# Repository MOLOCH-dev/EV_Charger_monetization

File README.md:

# EV_Charger_monetization
Internship under Magnes Motors

# TABLE OF CONTENTS
- [HTTP Webserver on Arduino IDE](#http-webserver-on-arduino-ide)
- [Schematics]
    - [Power Management IC with ESP32](#IC-ESP32)
    - [Current and Voltage Sensor with ESP32](#current-and-voltage-sensor-with-ESP32)

# HTTP Webserver on Arduino IDE

## 1. Flash Code to ESP32

## 2. Connect to WiFi AP "Magnes" using an Android Device

## 3. Go to "http://192.168.4.1" in browser through Android

## 4. Input Watthours and press 'Submit'

## 5. Charge is displayed on the webpage

## 6. Press Back

# IC ESP32

# Current and Voltage Sensor with ESP32

# Flutter App Development

Installation instructions

For Ubuntu 20.04 :
```
    sudo apt purge openjdk-11-jre -y
    sudo apt autoremove
    java -v
    sudo apt update
    sudo apt install openjdk-8-jre
```

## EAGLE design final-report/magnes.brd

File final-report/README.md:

# Final Report

## Instructions:

1. you need to add following zip libraries in arduino library:
	- [ESPAsyncWebServer-master.zip](ESPAsyncWebServer-master.zip)
	- [AsyncTCP-master.zip](AsyncTCP-master.zip)

2. Change ssid and password according to your wifi in the code and then upload the code to esp32.

3. Now open the serial monitor in arduino IDE, copy the ip address given there and paste it in google chrome tab.<br>
Enter your name, required ON time in minutes and current value the power outlet will have started working in arduino serial monitor, you will get the amount to be paid.<br>
**NOTE:** if you by mistakely entered a greater value in minutes, in pcb board, press the switch to restard esp, in design board, power off the adapter and on it again to restart esp. you dont need to flash the code again.

***Precautions:*** Don't touch the pcb board when live ac current is connected to the relay of the board.

## Circuit Diagrams

**If having any doubts in circuit design
Contact Akshat Bhanushali
8080252000**

**Demo videos can be found [here](https://drive.google.com/drive/folders/1dX3jx_bcWb19_J7uATpOkhGvCnvLUn2F)**

## improvement areas

1. current sensor needs be included
2. esp wifi module needs to be used instead of whole esp dev kit
3. remove 7A relay and include 16A omron relay in pcb design
4. include smps so that another socket is not required for adapter
5. try restarting the esp by giving commands over wifi.

## Members:
1. Akshat B.
2. Dhruva G.
3. Anushree S.

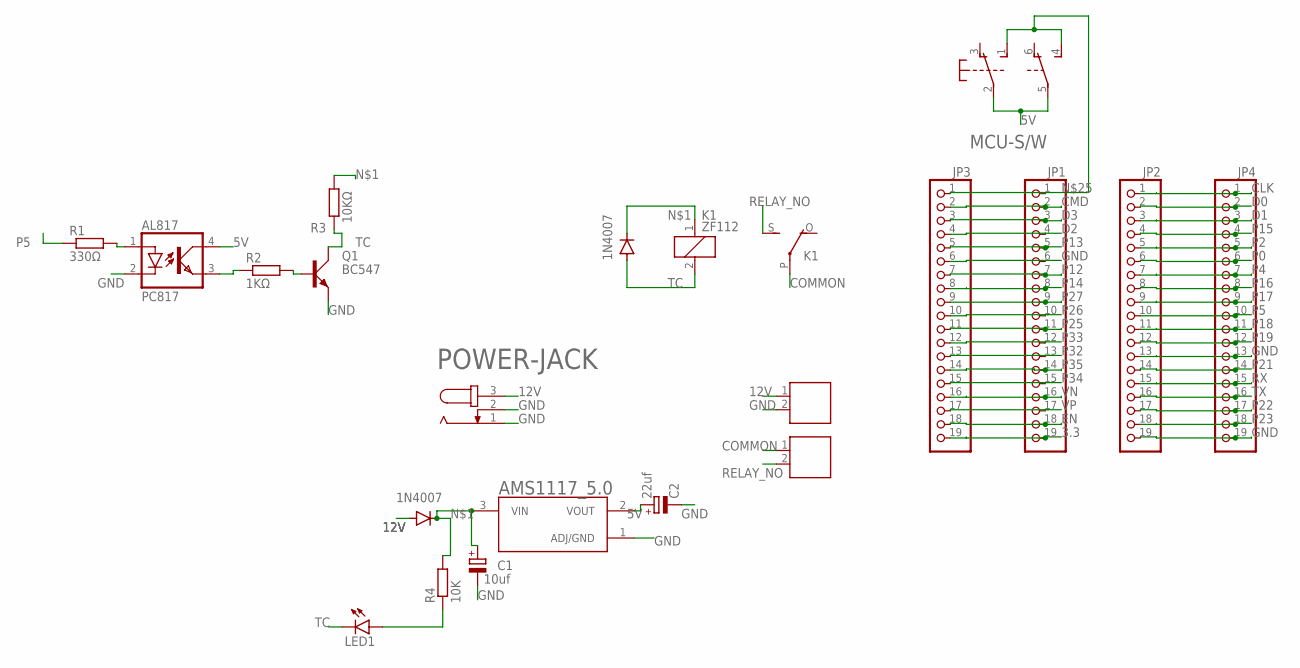
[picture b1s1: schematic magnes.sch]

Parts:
1N1: 1N4007; D-7.5
1N4007: DIODE-D-7.5; D-7.5
AL817: PC817; DIL04
AMS1117_5.0: AMS1117-3.3; SOT229P700X180-4N
C1: 10uf; E2,5-6
C2: 22uf; E2,5-6
JP1, JP2, JP3, JP4: PINHD-1X19; 1X19
K1: ZF112
LED1: LED3MM
MCU-S/W: 9077-2
PCBSCREWTERMINAL, PCBSCREWTERMINAL1: 691131710002
POWER-JACK: JACK-PLUG1; SPC4078
Q1: BC547; SOT54A
R1: 330Ω; 0204/7
R2: 1KΩ; 0204/7
R3: 10KΩ; 0204/7
R4: 10K; 0204/7

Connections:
3.3: JP1.19, JP3.19
5V: AL817.4 (COL), AMS1117_5.0.2 (VOUT), C2.+, MCU-S/W.2, MCU-S/W.5
12V: 1N4007.A, PCBSCREWTERMINAL.1, POWER-JACK.3
CLK: JP2.1, JP4.1
CMD: JP1.2, JP3.2
COMMON: K1.P, PCBSCREWTERMINAL1.1
D0: JP2.2, JP4.2
D1: JP2.3, JP4.3
D2: JP1.4, JP3.4
D3: JP1.3, JP3.3
EN: JP1.18, JP3.18
GND: AL817.2 (C), AMS1117_5.0.1 (ADJ/GND), C1.-, C2.-, JP1.6, JP2.13, JP2.19, JP3.6, JP4.13, JP4.19, PCBSCREWTERMINAL.2, POWER-JACK.1, POWER-JACK.2, Q1.E
unnamed: 1N1.C, 1N4007.C, AMS1117_5.0.3 (VIN), C1.+, K1.1, R3.2, R4.2
unnamed: Q1.B, R2.2
unnamed: AL817.1 (A), R1.2
unnamed: AL817.3 (EMIT), R2.1
unnamed: LED1.A, R4.1
unnamed: JP1.1, JP3.1, MCU-S/W.1 (S), MCU-S/W.4 (S)
P0: JP2.6, JP4.6
P2: JP2.5, JP4.5
P4: JP2.7, JP4.7
P5: JP2.10, JP4.10, R1.1
P12: JP1.7, JP3.7
P13: JP1.5, JP3.5
P14: JP1.8, JP3.8
P15: JP2.4, JP4.4
P16: JP2.8, JP4.8
P17: JP2.9, JP4.9
P18: JP2.11, JP4.11
P19: JP2.12, JP4.12
P21: JP2.14, JP4.14
P22: JP2.17, JP4.17
P23: JP2.18, JP4.18
P25: JP1.11, JP3.11
P26: JP1.10, JP3.10
P27: JP1.9, JP3.9
P32: JP1.13, JP3.13
P33: JP1.12, JP3.12
P34: JP1.15, JP3.15
P35: JP1.14, JP3.14
RELAY_NO: K1.S, PCBSCREWTERMINAL1.2
RX: JP2.15, JP4.15
TC: 1N1.A, K1.2, LED1.K (C), Q1.C, R3.1
TX: JP2.16, JP4.16
VN: JP1.16, JP3.16
VP: JP1.17, JP3.17

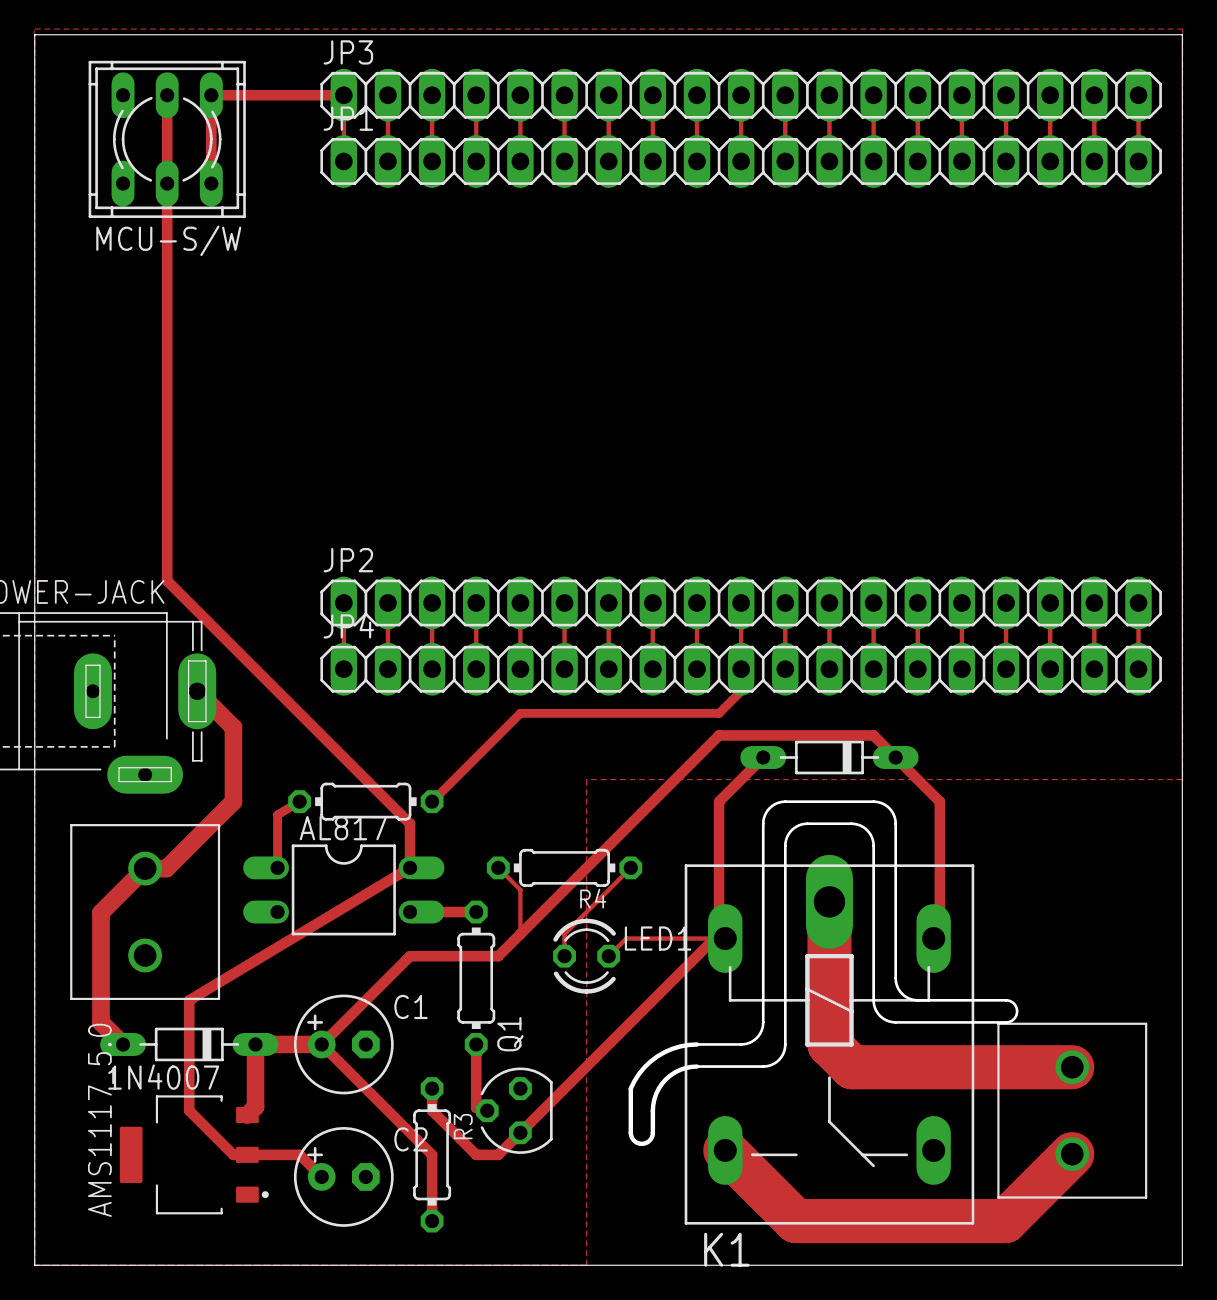
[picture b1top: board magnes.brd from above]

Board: 2 copper layers, 66.0 x 70.8 mm, 21 parts (0 on the bottom side), 46 nets.

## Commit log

2021-05-26 Arduino HTTP server
2021-05-31 ACS71020 IC with ESP32 Schematic
2021-06-07 Week 3
2021-06-21 Updated Java Dependencies
2021-08-24 start writing final report
2021-08-24 Add instructions to final-report
2021-08-24 add Kicad pic and also minor spell corrections
2021-08-24 add video link

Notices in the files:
parts and their libraries:
Wurth_Elektronik_Electromechanic_Termina: Copyright: Würth Elektronik
